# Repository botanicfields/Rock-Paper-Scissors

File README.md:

# Rock-Paper-Scissors
This is a beginner-friendly craft kit used at DIY events as a material for hands-on soldering.  

# じゃんけん判定器キット
- 初級用のはんだ付け教材を想定した電子工作キットです。  
- 地域イベントなどで、電子工作のはんだ付け体験（ハンズオン）に利用できます。  
- 不特定の来場者が短時間の参加で完成できる様、はんだ付け個所を24と少なくしています。  
- 難易度を下げるため、取り付ける部品はタクトスイッチのみとしています。  
- 安価な部品を使用し、コストを下げています。  

## 注意
- プリント基板やはんだには有毒な重金属(鉛など)が含まれています。
    - 工作した後や遊んだ後は、石鹸で手を洗ってください。
    - 小動物などがかじらない様にご注意ください。
    - 廃棄の際は自治体の指定に従ってください。
- 部品やはんだなどの突起物があります。
    - 部品や突起物に衣類を引っ掛けたり怪我をしないようご注意ください。
    - ケースやカバーを作成される場合は、四隅の穴をご利用ください。
- 小さなお子様には特にご注意ください。
    - プリント基板を舐めたりしない様、ご注意ください。
    - コイン電池などを飲み込まない様、ご注意ください。

## 内容物
- プリント基板(74x56mm, タクトスイッチ以外の部品は実装済) x1
- タクトスイッチ 赤 x3, 緑 x3
- コイン電池 CR2032 x1
- 説明書 x1  
※ケースやカバーは、ありません。  
※組み立てには、はんだ、はんだごてを含む工具が必要です。  

## 組み立て
### 1. プリント基板にタクトスイッチ6個を挿入します。
(1) 電池ホルダーを奥側に置いたとき、左側3個が緑、右側3個が赤です。  
  
(2) タクトスイッチがプリント基板に密着するまでしっかりと挿入します。  

### 2. はんだ付けします。  
(1) プリント基板を裏返し、タクトスイッチ6個分24個所全てをはんだ付けします。  

### 3. コイン電池(CR2032)を電池ホルダーに取り付けます。  
(1) コイン電池のプラス(+)を上にします。  
  
(2) 電池ホルダーの、スライドスイッチに近い方の金具に、コイン電池を差し込み引っ掛けます。  
  
(3) コイン電池の、電池ホルダーに引っ掛けた反対側を、押し込みます。  

## 遊び方
### 1. 電源を入れます。
(1) スライドスイッチをONの位置にします。オレンジ色が点灯します。  

### 2. じゃんけんをします。
(1) 赤と緑に分かれて遊びます。  
(2) 「じゃんけんポン！」で、赤の人と緑の人が各々「グー」、「チョキ」、「パー」のボタンのどれかを押します。  
(3) 赤色が点灯すれば赤の勝ち、緑色が点灯すれば緑の勝ち、黄色が点灯すれば「あいこ」です。  

### 3. 電源を切ります。
(1) 遊び終わったらスライドスイッチをONと反対の位置に戻します。  

## 説明書
- [説明書](./bf-043a_doc.pdf)  

## 回路図
- [回路図](./bf-043a_scm.pdf)  
- コイン電池(3V)で動作するよう74HCシリーズを使用し、Vf=2V程度のLEDを選択しています。
- 入手容易で安価なICを使うため、入力ボタンはハイサイドでプルダウン抵抗付きとし、出力もハイサイドで直接LEDを駆動しています。
- 明るさを合わせるため、緑LEDのみ電流制限抵抗を小さくしています。
- タクトスイッチのみ、はんだ付けハンズオン用にスルーホール部品を使用しています。赤色・緑色も選択できました。

## 実装図
- [実装図](./bf-043a_pcb.pdf)  

## 製造データ
- [KiCadデータ(単体)](./V01L02)  
- [製造データ(面付け12枚)](./V01L02/production)  
- 製造データは、JLCPCB "Fabrication Toolkit" により生成しました。

## ハンズオン開催イベント
- [電波文化祭⚡️サイクル3](https://scrapbox.io/denpa/%E3%83%9C%E3%82%BF%E3%83%8B%E3%83%83%E3%82%AF@%E9%9B%BB%E5%AD%90%E5%B7%A5%E4%BD%9C%E5%A5%BD%E3%81%8D_JK1TZG%E2%9A%A1%EF%B8%8F%E3%82%B5%E3%82%A4%E3%82%AF%E3%83%AB3)

以上

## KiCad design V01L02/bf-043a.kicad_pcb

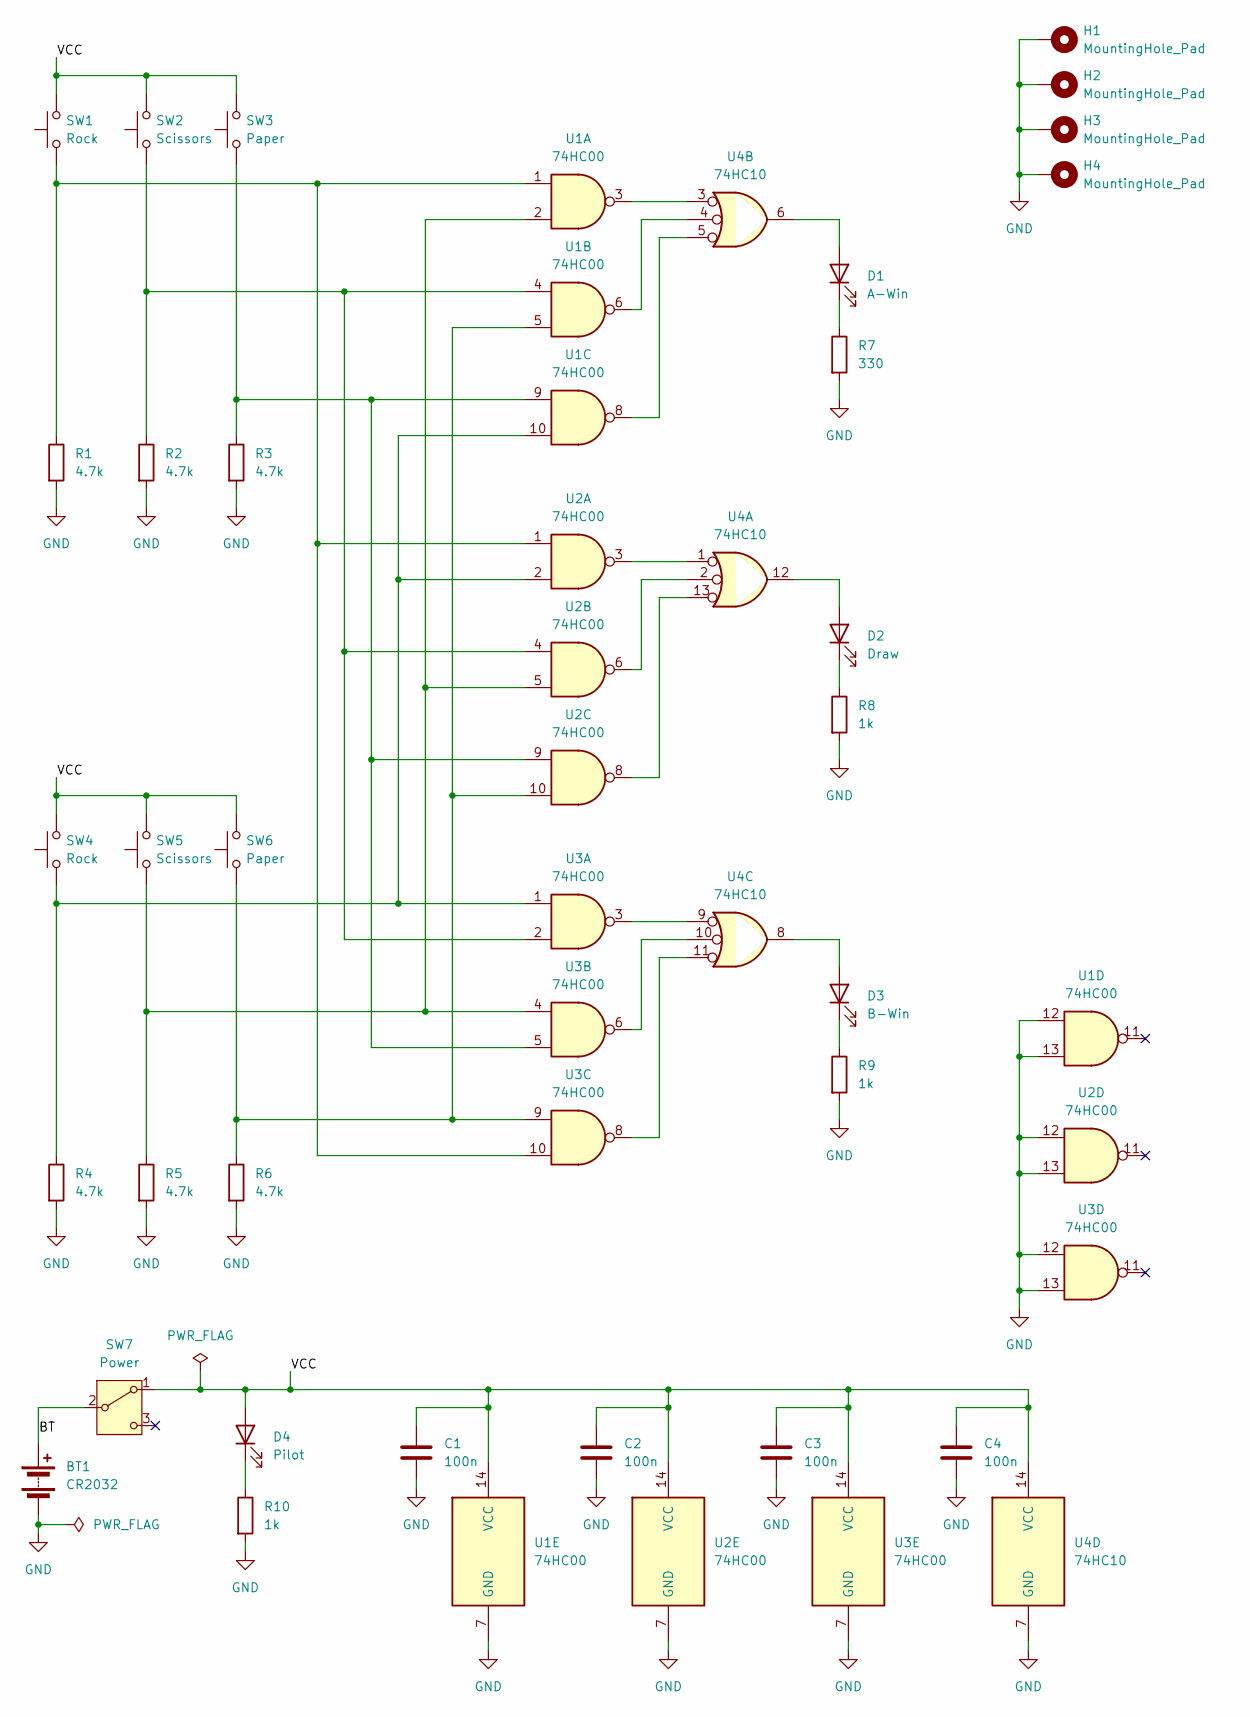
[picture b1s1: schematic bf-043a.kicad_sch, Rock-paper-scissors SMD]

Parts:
BT1: CR2032; BF@QJ-BS-6
C1, C2, C3, C4: 100n; C_0603_1608Metric
D1: A-Win; LED_0603_1608Metric
D2: Draw; LED_0603_1608Metric
D3: B-Win; LED_0603_1608Metric
D4: Pilot; LED_0603_1608Metric
H1, H2, H3, H4: MountingHole_Pad; MountingHole_3.2mm_M3_Pad
R1, R2, R3, R4, R5, R6: 4.7k; R_0603_1608Metric
R7: 330; R_0603_1608Metric
R8, R9, R10: 1k; R_0603_1608Metric
SW1, SW4: Rock; SW_PUSH_6mm_H5mm
SW2, SW5: Scissors; SW_PUSH_6mm_H5mm
SW3, SW6: Paper; SW_PUSH_6mm_H5mm
SW7: Power; SW_SPDT_PCM12
U1, U2, U3: 74HC00; SO-14_3.9x8.65mm_P1.27mm
U4: 74HC10; SO-14_3.9x8.65mm_P1.27mm

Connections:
/BT: BT1.1 (+), SW7.2 (B)
/VCC: C1.1, C2.1, C3.1, C4.1, D4.2 (A), SW1.2, SW2.2, SW3.2, SW4.2, SW5.2, SW6.2, SW7.1 (A), U1.14 (VCC), U2.14 (VCC), U3.14 (VCC), U4.14 (VCC)
GND: BT1.2 (-), C1.2, C2.2, C3.2, C4.2, H1.1, H2.1, H3.1, H4.1, R1.2, R2.2, R3.2, R4.2, R5.2, R6.2, R7.2, R8.2, R9.2, R10.2, U1.7 (GND), U1.12, U1.13, U2.7 (GND), U2.12, U2.13, U3.7 (GND), U3.12, U3.13, U4.7 (GND)
unnamed: D1.2 (A), U4.6
unnamed: D1.1 (K), R7.1
unnamed: D2.2 (A), U4.12
unnamed: D2.1 (K), R8.1
unnamed: D3.2 (A), U4.8
unnamed: D3.1 (K), R9.1
unnamed: D4.1 (K), R10.1
unnamed: R1.1, SW1.1, U1.1, U2.1, U3.10
unnamed: R2.1, SW2.1, U1.4, U2.4, U3.2
unnamed: R3.1, SW3.1, U1.9, U2.9, U3.5
unnamed: R4.1, SW4.1, U1.10, U2.2, U3.1
unnamed: R5.1, SW5.1, U1.2, U2.5, U3.4
unnamed: R6.1, SW6.1, U1.5, U2.10, U3.9
unnamed: U1.3, U4.3
unnamed: U1.6, U4.4
unnamed: U1.8, U4.5
unnamed: U2.3, U4.1
unnamed: U2.6, U4.2
unnamed: U2.8, U4.13
unnamed: U3.3, U4.9
unnamed: U3.6, U4.10
unnamed: U3.8, U4.11

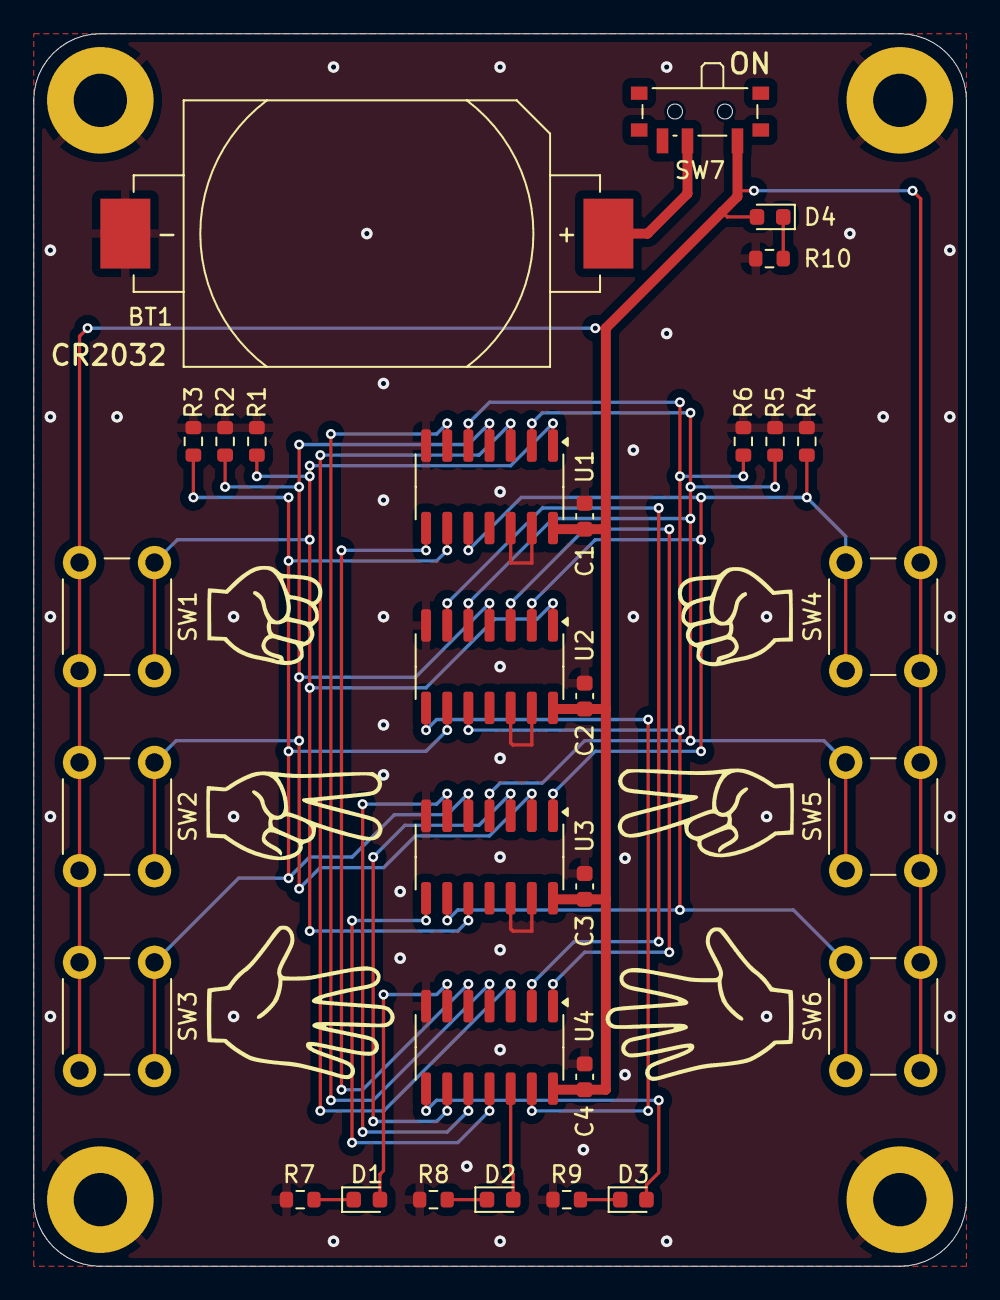
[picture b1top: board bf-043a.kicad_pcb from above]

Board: 2 copper layers, 56.0 x 74.0 mm, 34 parts (0 on the bottom side), 25 nets.

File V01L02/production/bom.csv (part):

Designator,Footprint,Quantity,Value,LCSC Part #
"BT1_12, BT1_11, BT1_10, BT1_9, BT1_8, BT1_7, BT1_6, BT1_5, BT1_4, BT1_3, BT1_2, BT1",BF@QJ-BS-6,12,CR2032,C70377
"C1_12, C1_11, C1_10, C1_9, C1_8, C1_7, C1_6, C1_5, C1_4, C1_3, C1_2, C1, C2_12, C2_11, C2_10, C2_9, C2_8, C2_7, C2_6, C2_5, C2_4, C2_3, C2_2, C2, C3_12, C3_11, C3_10, C3_9, C3_8, C3_7, C3_6, C3_5, C3_4, C3_3, C3_2, C3, C4_12, C4_11, C4_10, C4_9, C4_8, C4_7, C4_6, C4_5, C4_4, C4_3, C4_2, C4",0603,48,100n,C14663
"D1_12, D1_11, D1_10, D1_9, D1_8, D1_7, D1_6, D1_5, D1_4, D1_3, D1_2, D1",0603,12,A-Win,C965805
"D2_12, D2_11, D2_10, D2_9, D2_8, D2_7, D2_6, D2_5, D2_4, D2_3, D2_2, D2",0603,12,Draw,C72038
"D3_12, D3_11, D3_10, D3_9, D3_8, D3_7, D3_6, D3_5, D3_4, D3_3, D3_2, D3",0603,12,B-Win,C2286
"D4_12, D4_11, D4_10, D4_9, D4_8, D4_7, D4_6, D4_5, D4_4, D4_3, D4_2, D4",0603,12,Pilot,C7429913
"KiKit_MB_10_2, KiKit_MB_10_3, KiKit_MB_10_4, KiKit_MB_10_5, KiKit_MB_10_6, KiKit_MB_10_7, KiKit_MB_10_8, KiKit_MB_10_9, KiKit_MB_11_2, KiKit_MB_11_3, KiKit_MB_11_4, KiKit_MB_11_5, KiKit_MB_11_6, KiKit_MB_11_7, KiKit_MB_11_8, KiKit_MB_11_9, KiKit_MB_12_2, KiKit_MB_12_3, KiKit_MB_12_4, KiKit_MB_12_5, KiKit_MB_12_6, KiKit_MB_12_7, KiKit_MB_12_8, KiKit_MB_12_9, KiKit_MB_13_2, KiKit_MB_13_3, KiKit_MB_13_4, KiKit_MB_13_5, KiKit_MB_13_6, KiKit_MB_13_7, KiKit_MB_13_8, KiKit_MB_13_9, KiKit_MB_14_2, KiKit_MB_14_3, KiKit_MB_14_4, KiKit_MB_14_5, KiKit_MB_14_6, KiKit_MB_14_7, KiKit_MB_14_8, KiKit_MB_14_9, KiKit_MB_15_2, KiKit_MB_15_3, KiKit_MB_15_4, KiKit_MB_15_5, KiKit_MB_15_6, KiKit_MB_15_7, KiKit_MB_15_8, KiKit_MB_15_9, KiKit_MB_16_2, KiKit_MB_16_3, KiKit_MB_16_4, KiKit_MB_16_5, KiKit_MB_16_6, KiKit_MB_16_7, KiKit_MB_16_8, KiKit_MB_16_9, KiKit_MB_17_2, KiKit_MB_17_3, KiKit_MB_17_4, KiKit_MB_17_5, KiKit_MB_17_6, KiKit_MB_17_7, KiKit_MB_17_8, KiKit_MB_17_9, KiKit_MB_18_2, KiKit_MB_18_3, KiKit_MB_18_4, KiKit_MB_18_5, KiKit_MB_18_6, KiKit_MB_18_7, KiKit_MB_18_8, KiKit_MB_18_9, KiKit_MB_19_2, KiKit_MB_19_3, KiKit_MB_19_4, KiKit_MB_19_5, KiKit_MB_19_6, KiKit_MB_19_7, KiKit_MB_19_8, KiKit_MB_19_9, KiKit_MB_1_2, KiKit_MB_1_3, KiKit_MB_1_4, KiKit_MB_1_5, KiKit_MB_1_6, KiKit_MB_1_7, KiKit_MB_1_8, KiKit_MB_1_9, KiKit_MB_20_2, KiKit_MB_20_3, KiKit_MB_20_4, KiKit_MB_20_5, KiKit_MB_20_6, KiKit_MB_20_7, KiKit_MB_20_8, KiKit_MB_20_9, KiKit_MB_21_2, KiKit_MB_21_3, KiKit_MB_21_4, KiKit_MB_21_5, KiKit_MB_21_6, KiKit_MB_21_7, KiKit_MB_21_8, KiKit_MB_21_9, KiKit_MB_22_2, KiKit_MB_22_3, KiKit_MB_22_4, KiKit_MB_22_5, KiKit_MB_22_6, KiKit_MB_22_7, KiKit_MB_22_8, KiKit_MB_22_9, KiKit_MB_23_2, KiKit_MB_23_3, KiKit_MB_23_4, KiKit_MB_23_5, KiKit_MB_23_6, KiKit_MB_23_7, KiKit_MB_23_8, KiKit_MB_23_9, KiKit_MB_24_2, KiKit_MB_24_3, KiKit_MB_24_4, KiKit_MB_24_5, KiKit_MB_24_6, KiKit_MB_24_7, KiKit_MB_24_8, KiKit_MB_24_9, KiKit_MB_25_2, KiKit_MB_25_3, KiKit_MB_25_4, KiKit_MB_25_5, KiKit_MB_25_6, KiKit_MB_25_7, KiKit_MB_25_8, KiKit_MB_25_9, KiKit_MB_26_2, KiKit_MB_26_3, KiKit_MB_26_4, KiKit_MB_26_5, KiKit_MB_26_6, KiKit_MB_26_7, KiKit_MB_26_8, KiKit_MB_26_9, KiKit_MB_27_2, KiKit_MB_27_3, KiKit_MB_27_4, KiKit_MB_27_5, KiKit_MB_27_6, KiKit_MB_27_7, KiKit_MB_27_8, KiKit_MB_27_9, KiKit_MB_28_2, KiKit_MB_28_3, KiKit_MB_28_4, KiKit_MB_28_5, KiKit_MB_28_6, KiKit_MB_28_7, KiKit_MB_28_8, KiKit_MB_28_9, KiKit_MB_29_2, KiKit_MB_29_3, KiKit_MB_29_4, KiKit_MB_29_5, KiKit_MB_29_6, KiKit_MB_29_7, KiKit_MB_29_8, KiKit_MB_29_9, KiKit_MB_2_2, KiKit_MB_2_3, KiKit_MB_2_4, KiKit_MB_2_5, KiKit_MB_2_6, KiKit_MB_2_7, KiKit_MB_2_8, KiKit_MB_2_9, KiKit_MB_30_2, KiKit_MB_30_3, KiKit_MB_30_4, KiKit_MB_30_5, KiKit_MB_30_6, KiKit_MB_30_7, KiKit_MB_30_8, KiKit_MB_30_9, KiKit_MB_31_2, KiKit_MB_31_3, KiKit_MB_31_4, KiKit_MB_31_5, KiKit_MB_31_6, KiKit_MB_31_7, KiKit_MB_31_8, KiKit_MB_31_9, KiKit_MB_32_2, KiKit_MB_32_3, KiKit_MB_32_4, KiKit_MB_32_5, KiKit_MB_32_6, KiKit_MB_32_7, KiKit_MB_32_8, KiKit_MB_32_9",NPTH,200,NPTH,
"KiKit_MB_33_2, KiKit_MB_33_3, KiKit_MB_33_4, KiKit_MB_33_5, KiKit_MB_33_6, KiKit_MB_33_7, KiKit_MB_33_8, KiKit_MB_33_9, KiKit_MB_34_2, KiKit_MB_34_3, KiKit_MB_34_4, KiKit_MB_34_5, KiKit_MB_34_6, KiKit_MB_34_7, KiKit_MB_34_8, KiKit_MB_34_9, KiKit_MB_35_2, KiKit_MB_35_3, KiKit_MB_35_4, KiKit_MB_35_5, KiKit_MB_35_6, KiKit_MB_35_7, KiKit_MB_35_8, KiKit_MB_35_9, KiKit_MB_36_2, KiKit_MB_36_3, KiKit_MB_36_4, KiKit_MB_36_5, KiKit_MB_36_6, KiKit_MB_36_7, KiKit_MB_36_8, KiKit_MB_36_9, KiKit_MB_37_2, KiKit_MB_37_3, KiKit_MB_37_4, KiKit_MB_37_5, KiKit_MB_37_6, KiKit_MB_37_7, KiKit_MB_37_8, KiKit_MB_37_9, KiKit_MB_38_2, KiKit_MB_38_3, KiKit_MB_38_4, KiKit_MB_38_5, KiKit_MB_38_6, KiKit_MB_38_7, KiKit_MB_38_8, KiKit_MB_38_9, KiKit_MB_39_2, KiKit_MB_39_3, KiKit_MB_39_4, KiKit_MB_39_5, KiKit_MB_39_6, KiKit_MB_39_7, KiKit_MB_39_8, KiKit_MB_39_9, KiKit_MB_3_2, KiKit_MB_3_3, KiKit_MB_3_4, KiKit_MB_3_5, KiKit_MB_3_6, KiKit_MB_3_7, KiKit_MB_3_8, KiKit_MB_3_9, KiKit_MB_40_2, KiKit_MB_40_3, KiKit_MB_40_4, KiKit_MB_40_5, KiKit_MB_40_6, KiKit_MB_40_7, KiKit_MB_40_8, KiKit_MB_40_9, KiKit_MB_41_2, KiKit_MB_41_3, KiKit_MB_41_4, KiKit_MB_41_5, KiKit_MB_41_6, KiKit_MB_41_7, KiKit_MB_41_8, KiKit_MB_41_9, KiKit_MB_42_2, KiKit_MB_42_3, KiKit_MB_42_4, KiKit_MB_42_5, KiKit_MB_42_6, KiKit_MB_42_7, KiKit_MB_42_8, KiKit_MB_42_9, KiKit_MB_43_2, KiKit_MB_43_3, KiKit_MB_43_4, KiKit_MB_43_5, KiKit_MB_43_6, KiKit_MB_43_7, KiKit_MB_43_8, KiKit_MB_43_9, KiKit_MB_44_2, KiKit_MB_44_3, KiKit_MB_44_4, KiKit_MB_44_5, KiKit_MB_44_6, KiKit_MB_44_7, KiKit_MB_44_8, KiKit_MB_44_9, KiKit_MB_45_2, KiKit_MB_45_3, KiKit_MB_45_4, KiKit_MB_45_5, KiKit_MB_45_6, KiKit_MB_45_7, KiKit_MB_45_8, KiKit_MB_45_9, KiKit_MB_46_2, KiKit_MB_46_3, KiKit_MB_46_4, KiKit_MB_46_5, KiKit_MB_46_6, KiKit_MB_46_7, KiKit_MB_46_8, KiKit_MB_46_9, KiKit_MB_47_2, KiKit_MB_47_3, KiKit_MB_47_4, KiKit_MB_47_5, KiKit_MB_47_6, KiKit_MB_47_7, KiKit_MB_47_8, KiKit_MB_47_9, KiKit_MB_48_2, KiKit_MB_48_3, KiKit_MB_48_4, KiKit_MB_48_5, KiKit_MB_48_6, KiKit_MB_48_7, KiKit_MB_48_8, KiKit_MB_48_9, KiKit_MB_49_3, KiKit_MB_49_4, KiKit_MB_49_5, KiKit_MB_49_6, KiKit_MB_49_7, KiKit_MB_49_8, KiKit_MB_4_2, KiKit_MB_4_3, KiKit_MB_4_4, KiKit_MB_4_5, KiKit_MB_4_6, KiKit_MB_4_7, KiKit_MB_4_8, KiKit_MB_4_9, KiKit_MB_50_3, KiKit_MB_50_4, KiKit_MB_50_5, KiKit_MB_50_6, KiKit_MB_50_7, KiKit_MB_50_8, KiKit_MB_51_3, KiKit_MB_51_4, KiKit_MB_51_5, KiKit_MB_51_6, KiKit_MB_51_7, KiKit_MB_51_8, KiKit_MB_52_3, KiKit_MB_52_4, KiKit_MB_52_5, KiKit_MB_52_6, KiKit_MB_52_7, KiKit_MB_52_8, KiKit_MB_5_2, KiKit_MB_5_3, KiKit_MB_5_4, KiKit_MB_5_5, KiKit_MB_5_6, KiKit_MB_5_7, KiKit_MB_5_8, KiKit_MB_5_9, KiKit_MB_6_2, KiKit_MB_6_3, KiKit_MB_6_4, KiKit_MB_6_5, KiKit_MB_6_6, KiKit_MB_6_7, KiKit_MB_6_8, KiKit_MB_6_9, KiKit_MB_7_2, KiKit_MB_7_3, KiKit_MB_7_4, KiKit_MB_7_5, KiKit_MB_7_6, KiKit_MB_7_7, KiKit_MB_7_8, KiKit_MB_7_9, KiKit_MB_8_2, KiKit_MB_8_3, KiKit_MB_8_4, KiKit_MB_8_5, KiKit_MB_8_6, KiKit_MB_8_7, KiKit_MB_8_8, KiKit_MB_8_9",NPTH,200,NPTH,
"KiKit_MB_9_2, KiKit_MB_9_3, KiKit_MB_9_4, KiKit_MB_9_5, KiKit_MB_9_6, KiKit_MB_9_7, KiKit_MB_9_8, KiKit_MB_9_9",NPTH,8,NPTH,
"R1_12, R1_11, R1_10, R1_9, R1_8, R1_7, R1_6, R1_5, R1_4, R1_3, R1_2, R1, R2_12, R2_11, R2_10, R2_9, R2_8, R2_7, R2_6, R2_5, R2_4, R2_3, R2_2, R2, R3_12, R3_11, R3_10, R3_9, R3_8, R3_7, R3_6, R3_5, R3_4, R3_3, R3_2, R3, R4_12, R4_11, R4_10, R4_9, R4_8, R4_7, R4_6, R4_5, R4_4, R4_3, R4_2, R4, R5_12, R5_11, R5_10, R5_9, R5_8, R5_7, R5_6, R5_5, R5_4, R5_3, R5_2, R5, R6_12, R6_11, R6_10, R6_9, R6_8, R6_7, R6_6, R6_5, R6_4, R6_3, R6_2, R6",0603,72,4.7k,C23162
"R10_12, R10_11, R10_10, R10_9, R10_8, R10_7, R10_6, R10_5, R10_4, R10_3, R10_2, R10, R8_12, R8_11, R8_10, R8_9, R8_8, R8_7, R8_6, R8_5, R8_4, R8_3, R8_2, R8, R9_12, R9_11, R9_10, R9_9, R9_8, R9_7, R9_6, R9_5, R9_4, R9_3, R9_2, R9",0603,36,1k,C21190
"R7_12, R7_11, R7_10, R7_9, R7_8, R7_7, R7_6, R7_5, R7_4, R7_3, R7_2, R7",0603,12,330,C23138
"SW1_12, SW1_11, SW1_10, SW1_9, SW1_8, SW1_7, SW1_6, SW1_5, SW1_4, SW1_3, SW1_2, SW1, SW4_12, SW4_11, SW4_10, SW4_9, SW4_8, SW4_7, SW4_6, SW4_5, SW4_4, SW4_3, SW4_2, SW4",SW_PUSH_6mm_H5mm,24,Rock,
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
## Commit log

2024-11-05 readme.md corrected
2024-11-05 .gitignore, .csv removed
2024-11-05 README.md markdown fixed
2024-11-05 README.md markdown test
2024-11-05 README.md Markdown fix
2024-11-05 Markdown fix
2024-11-05 add comment of fabrication data
2024-11-07 add doc.pdf

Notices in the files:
V01L02/bf-043a.kicad_pcb:
Copyright 2024, BotanicFields, Inc.
